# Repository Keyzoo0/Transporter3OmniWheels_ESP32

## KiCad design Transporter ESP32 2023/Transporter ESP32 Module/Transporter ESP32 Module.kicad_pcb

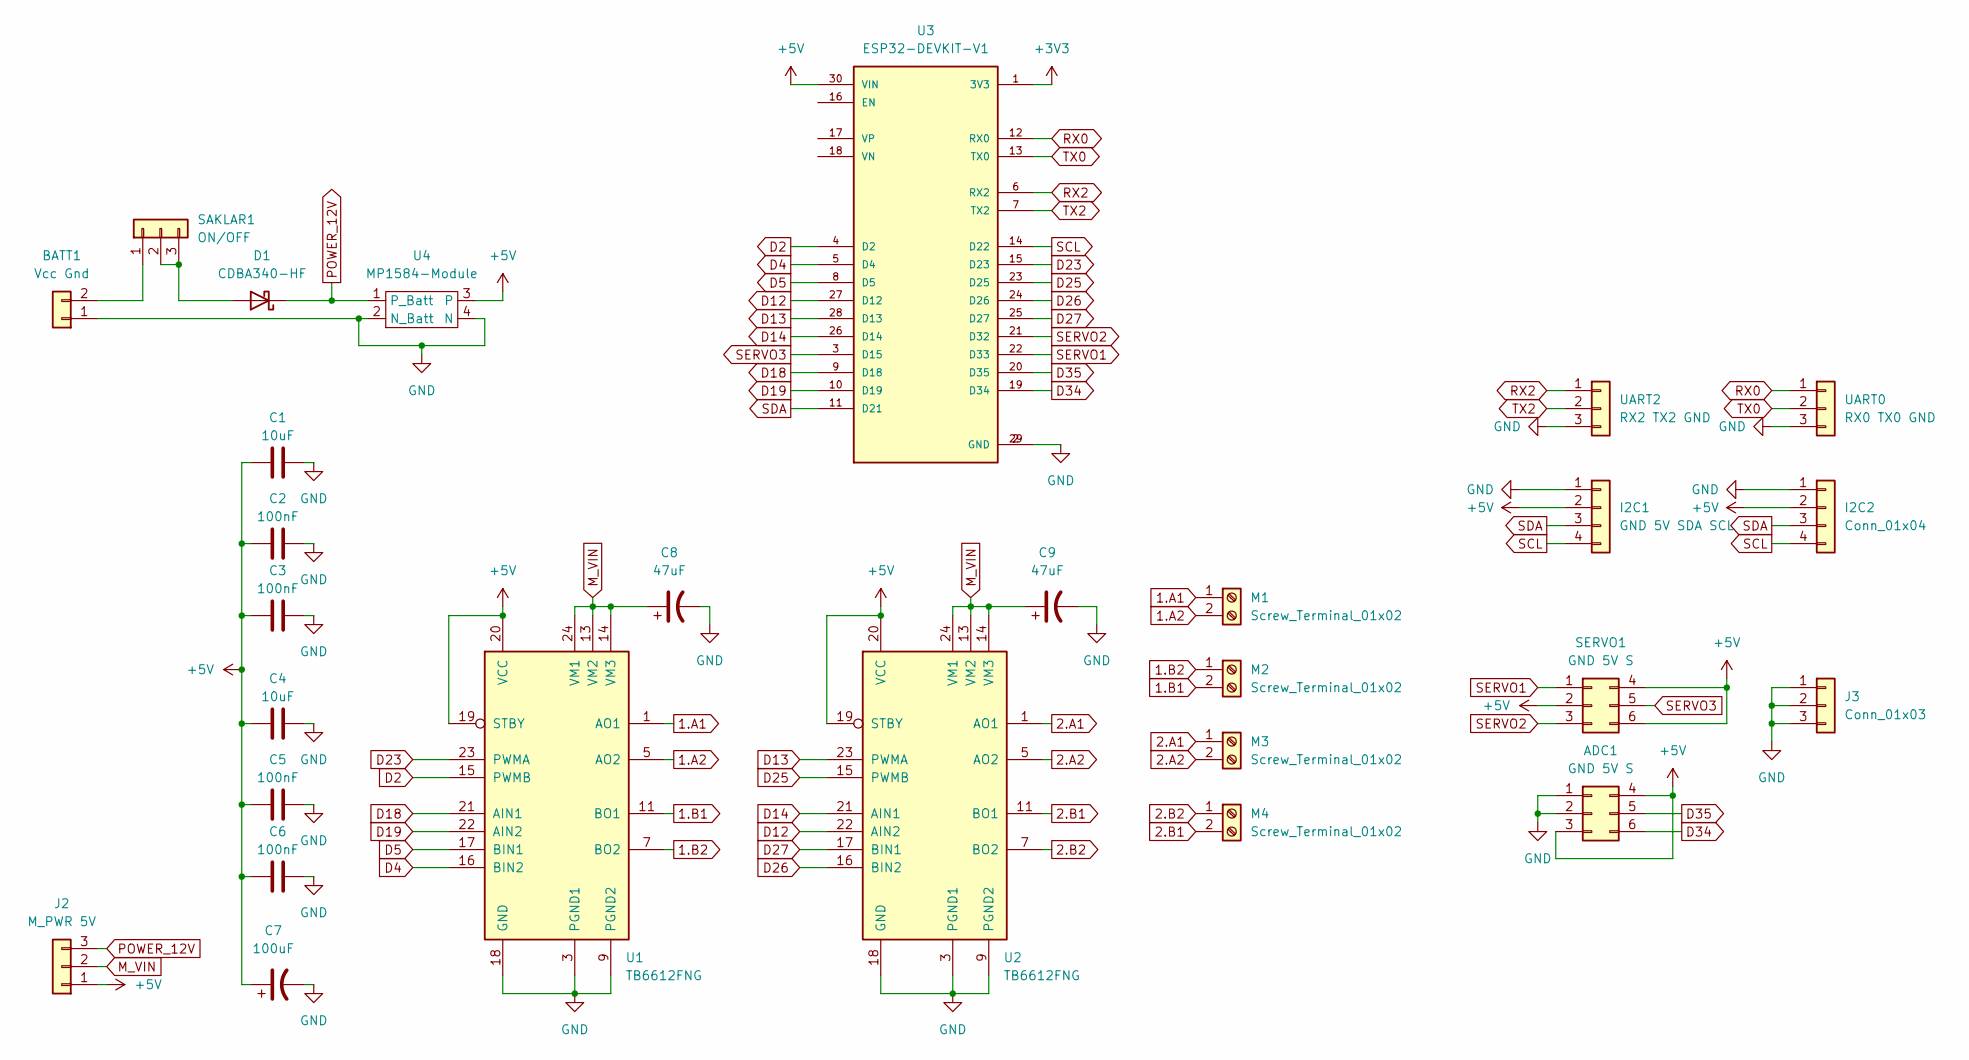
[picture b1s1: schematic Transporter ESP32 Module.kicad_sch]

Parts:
ADC1: GND 5V S; PinHeader_2x03_P2.54mm_Vertical
BATT1: Vcc Gnd; PinHeader_1x02_P2.54mm_Vertical
C1, C4: 10uF; C_1206_3216Metric
C2, C3, C5, C6: 100nF; C_1206_3216Metric
C7: 100uF; C_Elec_6.3x5.4
C8, C9: 47uF; CP_EIA-3216-18_Kemet-A
D1: CDBA340-HF; D_SMA
I2C1: GND 5V SDA SCL; PinHeader_1x04_P2.54mm_Vertical
I2C2: Conn_01x04; PinHeader_1x04_P2.54mm_Vertical
J2: M_PWR 5V; PinHeader_1x03_P2.54mm_Vertical
J3: Conn_01x03; PinHeader_1x03_P2.54mm_Vertical
M1, M2, M3, M4: Screw_Terminal_01x02; TerminalBlock_bornier-2_P5.08mm
SAKLAR1: ON/OFF; PinHeader_1x03_P2.54mm_Vertical
SERVO1: GND 5V S; PinHeader_2x03_P2.54mm_Vertical
U1, U2: TB6612FNG; SSOP-24_5.3x8.2mm_P0.65mm
U3: ESP32-DEVKIT-V1; PARTREV N/A
U4: MP1584-Module
UART0: RX0 TX0 GND; PinHeader_1x03_P2.54mm_Vertical
UART2: RX2 TX2 GND; PinHeader_1x03_P2.54mm_Vertical

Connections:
1.A1: M1.1, U1.1 (AO1), U1.2 (AO1)
1.A2: M1.2, U1.5 (AO2), U1.6 (AO2)
1.B1: M2.2, U1.11 (BO1), U1.12 (BO1)
1.B2: M2.1, U1.7 (BO2), U1.8 (BO2)
2.A1: M3.1, U2.1 (AO1), U2.2 (AO1)
2.A2: M3.2, U2.5 (AO2), U2.6 (AO2)
2.B1: M4.2, U2.11 (BO1), U2.12 (BO1)
2.B2: M4.1, U2.7 (BO2), U2.8 (BO2)
+3V3: U3.1 (3V3)
+5V: ADC1.3, ADC1.4, C1.1, C2.1, C3.1, C4.1, C5.1, C6.1, C7.1, I2C1.2, I2C2.2, J2.1, SERVO1.2, SERVO1.4, SERVO1.6, U1.19 (STBY), U1.20 (VCC), U2.19 (STBY), U2.20 (VCC), U3.30 (VIN), U4.3
D2: U1.15 (PWMB), U3.4 (D2)
D4: U1.16 (BIN2), U3.5 (D4)
D5: U1.17 (BIN1), U3.8 (D5)
D12: U2.22 (AIN2), U3.27 (D12)
D13: U2.23 (PWMA), U3.28 (D13)
D14: U2.21 (AIN1), U3.26 (D14)
D18: U1.21 (AIN1), U3.9 (D18)
D19: U1.22 (AIN2), U3.10 (D19)
D23: U1.23 (PWMA), U3.15 (D23)
D25: U2.15 (PWMB), U3.23 (D25)
D26: U2.16 (BIN2), U3.24 (D26)
D27: U2.17 (BIN1), U3.25 (D27)
D34: ADC1.6, U3.19 (D34)
D35: ADC1.5, U3.20 (D35)
GND: ADC1.1, ADC1.2, BATT1.1, C1.2, C2.2, C3.2, C4.2, C5.2, C6.2, C7.2, C8.2, C9.2, I2C1.1, I2C2.1, J3.1, J3.2, J3.3, U1.3 (PGND1), U1.4 (PGND1), U1.9 (PGND2), U1.10 (PGND2), U1.18 (GND), U2.3 (PGND1), U2.4 (PGND1), U2.9 (PGND2), U2.10 (PGND2), U2.18 (GND), U3.2 (GND), U3.29 (GND), U4.2 (N_Batt), U4.4 (N), UART0.3, UART2.3
M_VIN: C8.1, C9.1, J2.2, U1.13 (VM2), U1.14 (VM3), U1.24 (VM1), U2.13 (VM2), U2.14 (VM3), U2.24 (VM1)
unnamed: BATT1.2, SAKLAR1.1
unnamed: D1.2 (A), SAKLAR1.2, SAKLAR1.3
POWER_12V: D1.1 (K), J2.3, U4.1 (P_Batt)
RX0: U3.12 (RX0), UART0.1
RX2: U3.6 (RX2), UART2.1
SCL: I2C1.4, I2C2.4, U3.14 (D22)
SDA: I2C1.3, I2C2.3, U3.11 (D21)
SERVO1: SERVO1.1, U3.22 (D33)
SERVO2: SERVO1.3, U3.21 (D32)
SERVO3: SERVO1.5, U3.3 (D15)
TX0: U3.13 (TX0), UART0.2
TX2: U3.7 (TX2), UART2.2

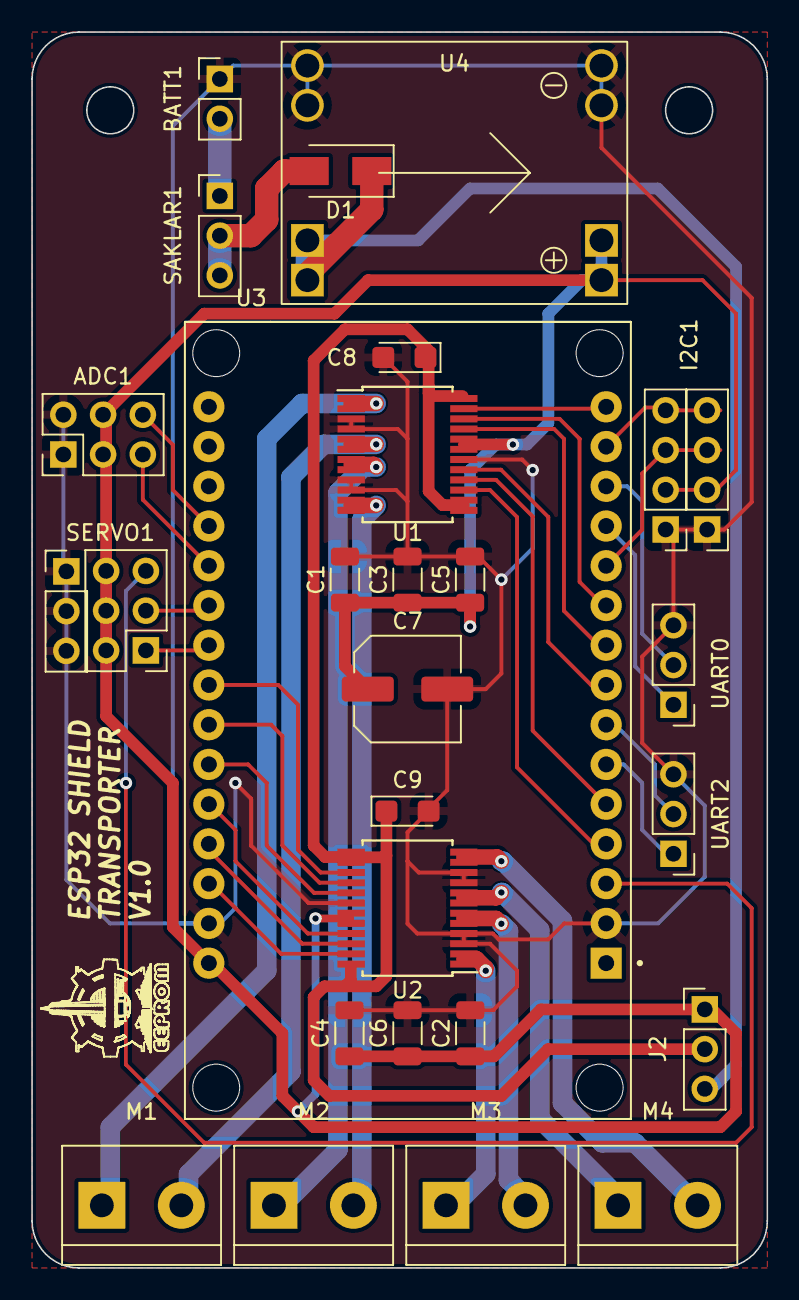
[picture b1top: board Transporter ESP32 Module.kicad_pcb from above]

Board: 2 copper layers, 47.0 x 79.0 mm, 28 parts (0 on the bottom side), 37 nets.

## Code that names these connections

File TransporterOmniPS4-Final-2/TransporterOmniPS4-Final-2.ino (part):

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
// setup actuator
/////////////////////////////////////////////////
#define servo1 17
#define servo2 16
#define servo3 5
#define servo4 23
//contruct servo
Servo capit1;
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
